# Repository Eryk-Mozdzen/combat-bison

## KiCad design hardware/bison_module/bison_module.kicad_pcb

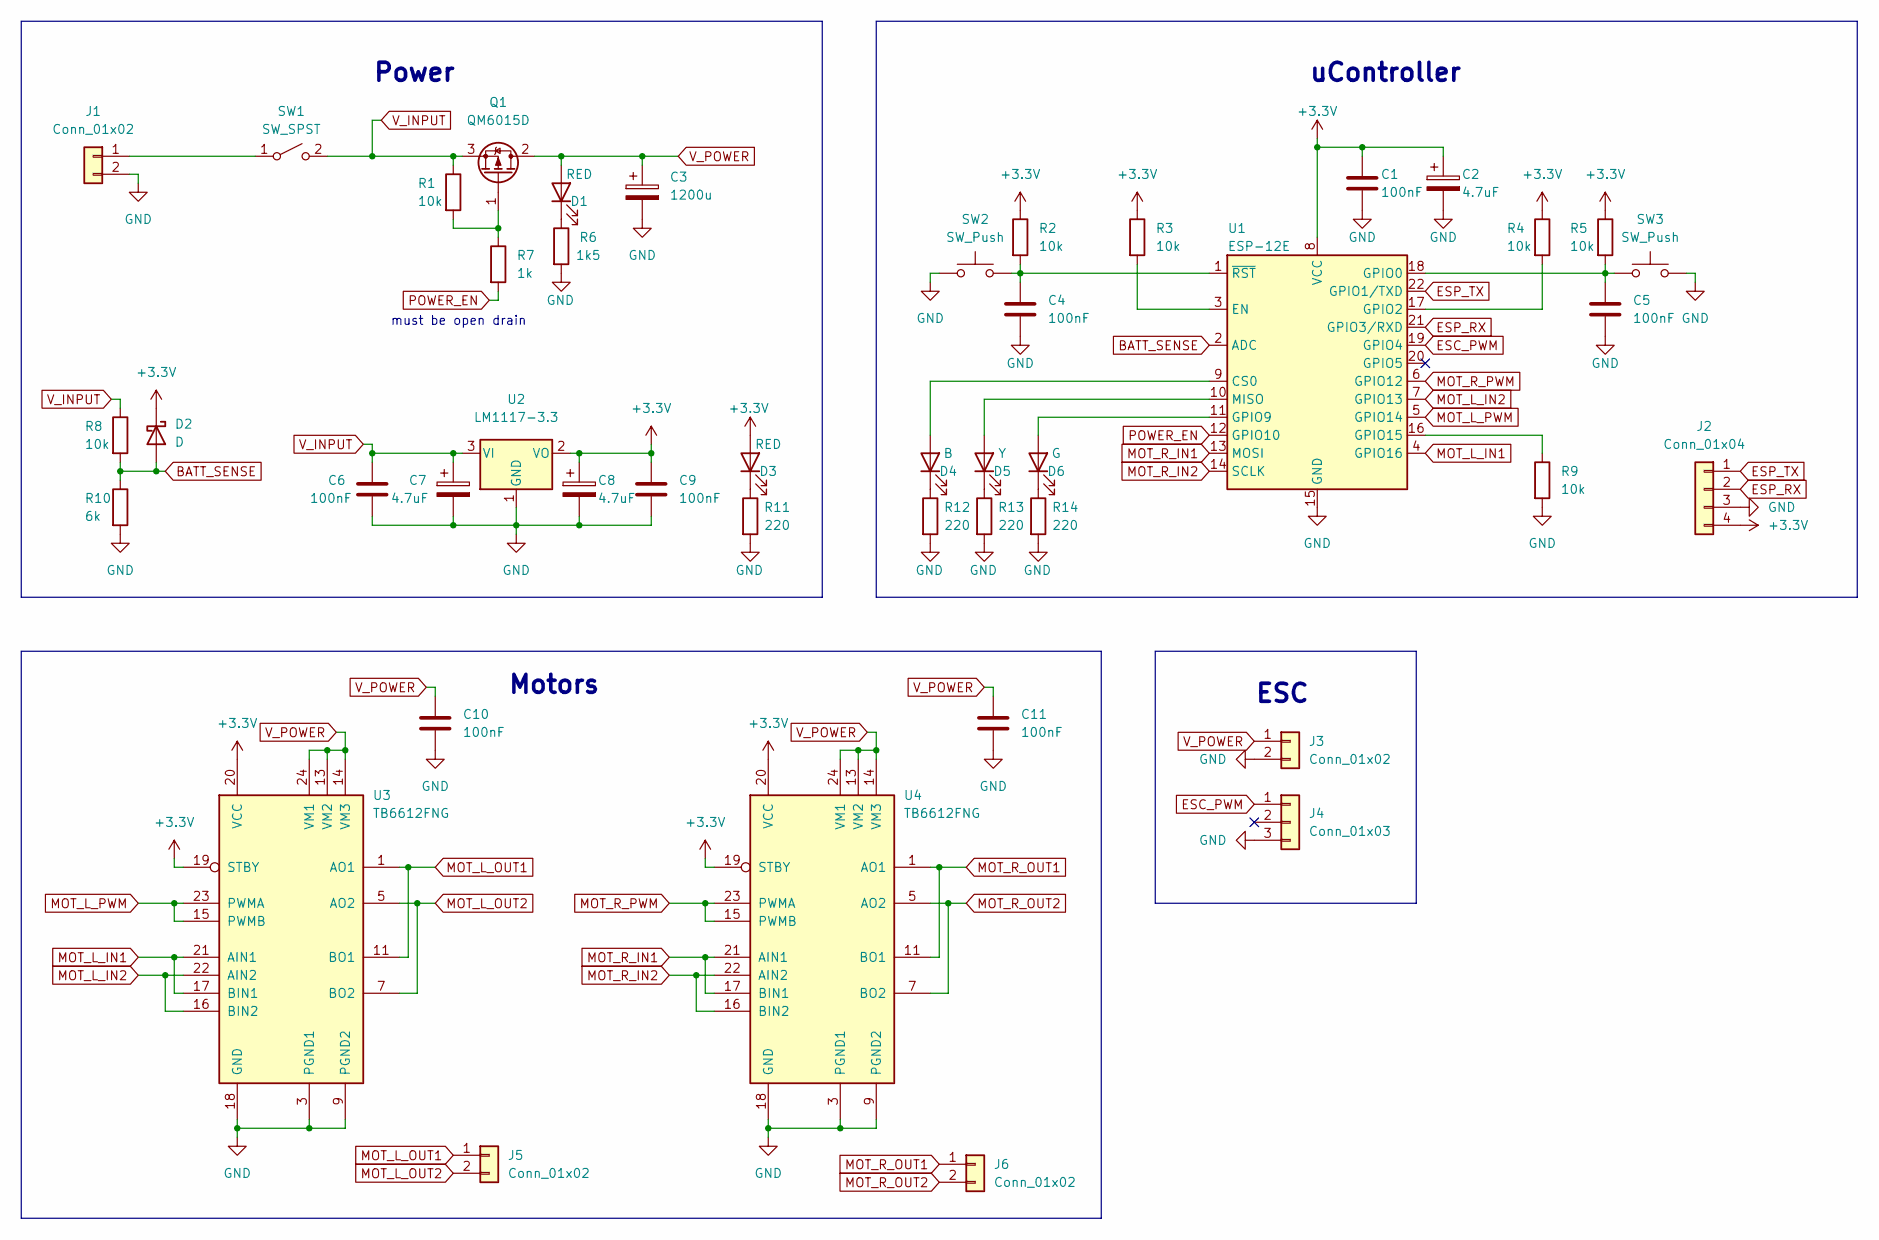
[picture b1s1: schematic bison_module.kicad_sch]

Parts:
C1, C4, C5, C6, C9, C10, C11: 100nF; C_0805_2012Metric
C2, C7, C8: 4.7uF; CP_EIA-3216-18_Kemet-A
C3: 1200u; CP_Radial_D10.0mm_P7.50mm
D1, D3: RED; LED_0805_2012Metric
D2: D; D_0805_2012Metric
D4: B; LED_0805_2012Metric
D5: Y; LED_0805_2012Metric
D6: G; LED_0805_2012Metric
J1, J3: Conn_01x02; AMASS_XT30U-F_1x02_P5.0mm_Vertical
J2: Conn_01x04; PinHeader_1x04_P2.54mm_Vertical
J4: Conn_01x03; PinHeader_1x03_P2.54mm_Vertical
J5, J6: Conn_01x02; PinHeader_1x02_P2.54mm_Vertical
Q1: QM6015D; TO-252-2
R1, R2, R3, R4, R5, R8, R9: 10k; R_0805_2012Metric
R6: 1k5; R_0805_2012Metric
R7: 1k; R_0805_2012Metric
R10: 6k; R_0805_2012Metric
R11, R12, R13, R14: 220; R_0805_2012Metric
SW1: SW_SPST; AMASS_XT30U-F_1x02_P5.0mm_Vertical
SW2, SW3: SW_Push; SW_Push_1P1T_NO_6x6mm_H9.5mm
U1: ESP-12E
U2: LM1117-3.3; SOT-223-3_TabPin2
U3, U4: TB6612FNG; SSOP-24_5.3x8.2mm_P0.65mm

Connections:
+3V3: C1.1, C2.1, C8.1, C9.1, D2.1 (K), D3.2 (A), J2.4, R2.1, R3.1, R4.1, R5.1, U1.8 (VCC), U2.2 (VO), U3.19 (STBY), U3.20 (VCC), U4.19 (STBY), U4.20 (VCC)
BATT_SENSE: D2.2 (A), R8.2, R10.1, U1.2 (ADC)
ESC_PWM: J4.1, U1.19 (GPIO4)
ESP_RX: J2.2, U1.21 (GPIO3/RXD)
ESP_TX: J2.1, U1.22 (GPIO1/TXD)
GND: C1.2, C2.2, C3.2, C4.2, C5.2, C6.2, C7.2, C8.2, C9.2, C10.2, C11.2, J1.2, J2.3, J3.2, J4.3, R6.2, R9.2, R10.2, R11.2, R12.2, R13.2, R14.2, SW2.1, SW3.2, U1.15 (GND), U2.1 (GND), U3.3 (PGND1), U3.4 (PGND1), U3.9 (PGND2), U3.10 (PGND2), U3.18 (GND), U4.3 (PGND1), U4.4 (PGND1), U4.9 (PGND2), U4.10 (PGND2), U4.18 (GND)
MOT_L_IN1: U1.4 (GPIO16), U3.17 (BIN1), U3.21 (AIN1)
MOT_L_IN2: U1.7 (GPIO13), U3.16 (BIN2), U3.22 (AIN2)
MOT_L_OUT1: J5.1, U3.1 (AO1), U3.2 (AO1), U3.11 (BO1), U3.12 (BO1)
MOT_L_OUT2: J5.2, U3.5 (AO2), U3.6 (AO2), U3.7 (BO2), U3.8 (BO2)
MOT_L_PWM: U1.5 (GPIO14), U3.15 (PWMB), U3.23 (PWMA)
MOT_R_IN1: U1.13 (MOSI), U4.17 (BIN1), U4.21 (AIN1)
MOT_R_IN2: U1.14 (SCLK), U4.16 (BIN2), U4.22 (AIN2)
MOT_R_OUT1: J6.1, U4.1 (AO1), U4.2 (AO1), U4.11 (BO1), U4.12 (BO1)
MOT_R_OUT2: J6.2, U4.5 (AO2), U4.6 (AO2), U4.7 (BO2), U4.8 (BO2)
MOT_R_PWM: U1.6 (GPIO12), U4.15 (PWMB), U4.23 (PWMA)
unnamed: C4.1, R2.2, SW2.2, U1.1 (~RST)
unnamed: C5.1, R5.2, SW3.1, U1.18 (GPIO0)
unnamed: D1.1 (K), R6.1
unnamed: D3.1 (K), R11.1
unnamed: D4.1 (K), R12.1
unnamed: D4.2 (A), U1.9 (CS0)
unnamed: D5.1 (K), R13.1
unnamed: D5.2 (A), U1.10 (MISO)
unnamed: D6.1 (K), R14.1
unnamed: D6.2 (A), U1.11 (GPIO9)
unnamed: J1.1, SW1.1 (A)
unnamed: Q1.1 (G), R1.2, R7.1
unnamed: R3.2, U1.3 (EN)
unnamed: R4.2, U1.17 (GPIO2)
unnamed: R9.1, U1.16 (GPIO15)
POWER_EN: R7.2, U1.12 (GPIO10)
V_INPUT: C6.1, C7.1, Q1.3 (S), R1.1, R8.1, SW1.2 (B), U2.3 (VI)
V_POWER: C3.1, C10.1, C11.1, D1.2 (A), J3.1, Q1.2 (D), U3.13 (VM2), U3.14 (VM3), U3.24 (VM1), U4.13 (VM2), U4.14 (VM3), U4.24 (VM1)

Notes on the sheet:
uController
Motors
Power
must be open drain
ESC

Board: 2 copper layers, 45 parts (25 on the bottom side), 34 nets, no tracks yet.

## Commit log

2022-05-17 First commit with all current work
2022-06-16 add reverse engineered setup
2022-06-16 Działający RC z diodkami
2022-06-17 Sofrware i think workds
2022-06-20 begin of custom bcp
2022-06-21 ESP programming stuff
2022-06-21 more pcb layout
2022-07-09 add photos
2022-10-23 start new version
2022-10-23 motor gear
2024-06-24 bizon ultra
